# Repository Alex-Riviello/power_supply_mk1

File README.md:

# power_supply_mk1

## Description

Power supply created during ELE3000 - Personal project at Polytechnique Montreal (2017).  
The voltage is controlled by a PWM signal generated by a EFM8 Silicon Labs microcontroller. The signal is filtered and injected into the adjust pin of a LM337 and LM317 to generate a variable positive and negative voltage (got the idea from the EEVBlog#221 https://www.youtube.com/watch?v=CIGjActDeoM&t=860s). 

To communicate with the microcontroller, I used an Aardvark (USB to I2C Host Adapter). The voltage was set and the current was measured in real-time. Everything was displayed on a GUI made with PyQt.

## Project Details

TODO: Translate to english.

### Circuit Design

The PCB was designed using KiCAD. The KiCAD project can be found in the ./kicad_psu_mk1 directory.  
NOTE: This was one of my first PCB designs. I tried using many through-hole components to test them on a breadboard.

#### Schematic

#### PCB

#### Rectifier Bridge

A simple diode bridge was used to rectify the voltage coming out of the transformer.

#### Microcontroller

The EFM8BB1 microcontroller was used for this project. I chose this MCU since I had a couple laying around. A laptop communicates with the chip via I2C (and a USB to I2C adapter). I2C was used since it's a simple protocol that be used with a Raspberry Pi. The MCU also sends a PWM signal to the voltage regulators to modulate the output voltage.
2 ADCs are used to measure the voltage drop across a very small resistor to detect the current flowing through the outputs.

#### Positive voltage control

The voltage is controlled with a PWM signal which is filtered and amplified. An LM317 is used for the positive voltage and a LM337 is used for the negative voltage.

### GUI

The python GUI used is illustrated below. The voltage could be set and read in real-time. The code can be found in ./python_code. However, the hc file is not included (Aardvark interface), PyQt4 is no longer supported and the code runs in Python2. 

### Final Result

Overall, the PSU could provide upto 1.5 A of current at +/-2V to +/- 12.5V. The final circuit looked like this:

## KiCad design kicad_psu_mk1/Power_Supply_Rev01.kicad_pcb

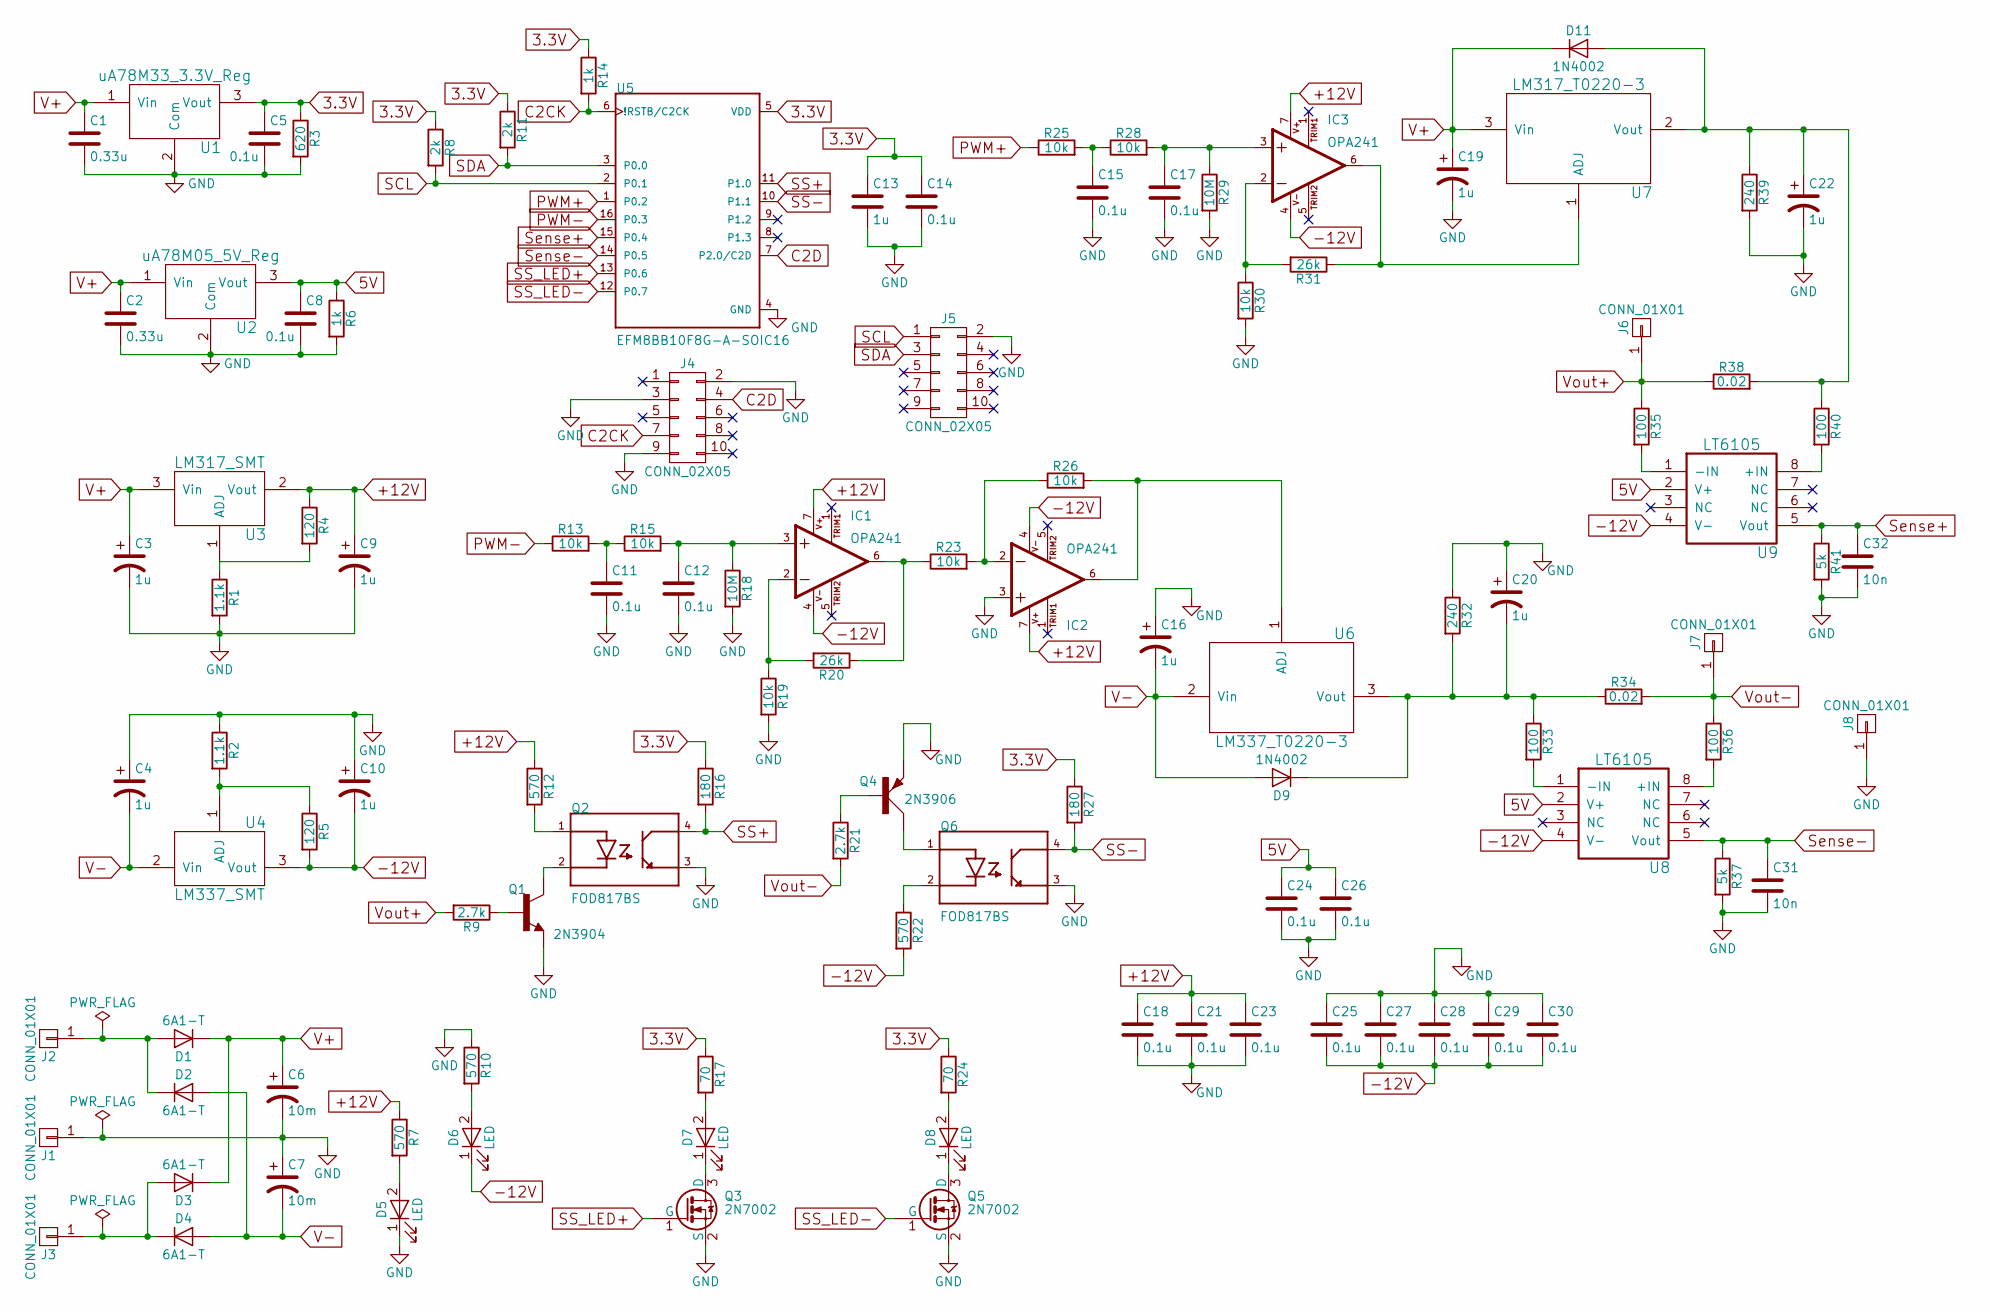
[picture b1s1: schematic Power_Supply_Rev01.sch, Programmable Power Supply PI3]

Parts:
C1, C2: 0.33u; C_0805_HandSoldering
C3, C4, C9, C10, C16, C19, C20, C22: 1u; CP_Tantalum_Case-A_EIA-3216-18_Hand
C5, C8, C11, C12, C14, C15, C17, C18, C21, C23, C24, C25, C26, C27, C28, C29, C30: 0.1u; C_0805_HandSoldering
C6, C7: 10m; CP_Radial_D22.0mm_P10.00mm_SnapIn
C13: 1u; C_0805_HandSoldering
C31, C32: 10n; C_0805_HandSoldering
D1, D2, D3, D4: 6A1-T; D_P600_R-6_P20.00mm_Horizontal
D5, D6, D7, D8: LED; LED_0805_HandSoldering
D9, D11: 1N4002; D_DO-41_SOD81_P7.62mm_Horizontal
IC1, IC2, IC3: OPA241; DIL08
J1, J2, J3, J6, J7, J8: CONN_01X01; SolderWirePad_single_SMD_5x10mm
J4, J5: CONN_02X05; Pin_Header_Straight_2x05_Pitch2.54mm
Q1: 2N3904; TO92
Q2, Q6: FOD817BS; SOIC254P1016X385-4N
Q3, Q5: 2N7002; SOT-23
Q4: 2N3906; TO92D
R1, R2: 1.1k; R_1206_HandSoldering
R3: 620; R_1206_HandSoldering
R4, R5: 120; R_1206_HandSoldering
R6, R14: 1k; R_1206_HandSoldering
R7, R10, R12, R22: 570; R_1206_HandSoldering
R8, R11: 2k; R_1206_HandSoldering
R9, R21: 2.7k; R_1206_HandSoldering
R13, R15, R19, R23, R25, R26, R28, R30: 10k; R_1206_HandSoldering
R16, R27: 180; R_1206_HandSoldering
R17, R24: 70; R_1206_HandSoldering
R18, R29: 10M; R_1206_HandSoldering
R20, R31: 26k; R_1206_HandSoldering
R32, R39: 240; R_2512_HandSoldering
R33, R35, R36, R40: 100; R_1206_HandSoldering
R34, R38: 0.02; R_1206_HandSoldering
R37, R41: 5k; R_1206_HandSoldering
U1: uA78M33_3.3V_Reg; SOT230P700X180-4N
U2: uA78M05_5V_Reg; SOT230P700X180-4N
U3: LM317_SMT; SOT230P700X180-4N
U4: LM337_SMT; SOT230P700X180-4N
U5: EFM8BB10F8G-A-SOIC16; SOIC127P600X175-16N
U6: LM337_T0220-3; TO-220-3_Horizontal
U7: LM317_T0220-3; TO-220-3_Horizontal
U8, U9: LT6105; MSOP-8_3x3mm_Pitch0.65mm

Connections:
3.3V: C5.1, C13.1, C14.1, R3.1, R8.1, R11.1, R14.1, R16.1, R17.1, R24.1, R27.1, U1.3 (Vout), U5.5 (VDD)
5V: C8.1, C24.1, C26.1, R6.1, U2.3 (Vout), U8.2 (V+), U9.2 (V+)
+12V: C9.1, C18.1, C21.1, C23.1, IC1.7 (V+), IC2.7 (V+), IC3.7 (V+), R4.1, R7.1, R12.1, U3.2 (Vout)
-12V: C10.2, C25.2, C27.2, C28.2, C29.2, C30.2, D6.1 (K), IC1.4 (V-), IC2.4 (V-), IC3.4 (V-), R5.2, R22.2, U4.3 (Vout), U8.4 (V-), U9.4 (V-)
C2CK: J4.7, R14.2, U5.6 (!RSTB/C2CK)
C2D: J4.4, U5.7 (P2.0/C2D)
GND: C1.2, C2.2, C3.2, C4.1, C5.2, C6.2, C7.1, C8.2, C9.2, C10.1, C11.2, C12.2, C13.2, C14.2, C15.2, C16.1, C17.2, C18.2, C19.2, C20.1, C21.2, C22.2, C23.2, C24.2, C25.1, C26.2, C27.1, C28.1, C29.1, C30.1, C31.2, C32.2, D5.1 (K), IC2.3 (+IN), J1.1, J4.2, J4.3, J4.9, J5.2, J8.1, Q1.3 (E), Q2.3 (EMITTER), Q3.2 (S), Q4.E, Q5.2 (S), Q6.3 (EMITTER), R1.2, R2.1, R3.2, R6.2, R10.1, R18.2, R19.2, R29.2, R30.2, R32.1, R37.2, R39.2, R41.2, U1.2 (Com), U2.2 (Com), U5.4 (GND)
unnamed: C11.1, R13.2, R15.1
unnamed: C12.1, IC1.3 (+IN), R15.2, R18.1
unnamed: C15.1, R25.2, R28.1
unnamed: C17.1, IC3.3 (+IN), R28.2, R29.1
unnamed: C20.2, D9.1 (K), R32.2, R33.1, R34.1, U6.3 (Vout)
unnamed: C22.1, D11.2 (A), R38.2, R39.1, R40.1, U7.2 (Vout)
unnamed: D1.2 (A), D2.1 (K), J2.1
unnamed: D3.2 (A), D4.1 (K), J3.1
unnamed: D5.2 (A), R7.2
unnamed: D6.2 (A), R10.2
unnamed: D7.1 (K), Q3.3 (D)
unnamed: D7.2 (A), R17.2
unnamed: D8.1 (K), Q5.3 (D)
unnamed: D8.2 (A), R24.2
unnamed: IC1.2 (-IN), R19.1, R20.2
unnamed: IC1.6 (OUT), R20.1, R23.1
unnamed: IC2.2 (-IN), R23.2, R26.1
unnamed: IC2.6 (OUT), R26.2, U6.1 (ADJ)
unnamed: IC3.2 (-IN), R30.1, R31.2
unnamed: IC3.6 (OUT), R31.1, U7.1 (ADJ)
unnamed: Q1.1 (C), Q2.2 (CATHODE)
unnamed: Q1.2 (B), R9.1
unnamed: Q2.1 (ANODE), R12.2
unnamed: Q4.B, R21.1
unnamed: Q4.C, Q6.1 (ANODE)
unnamed: Q6.2 (CATHODE), R22.1
unnamed: R1.1, R4.2, U3.1 (ADJ)
unnamed: R2.2, R5.1, U4.1 (ADJ)
unnamed: R33.2, U8.1 (-IN)
unnamed: R35.2, U9.1 (-IN)
unnamed: R36.2, U8.8 (+IN)
unnamed: R40.2, U9.8 (+IN)
PWM+: R25.1, U5.1 (P0.2)
PWM-: R13.1, U5.16 (P0.3)
SCL: J5.1, R8.2, U5.2 (P0.1)
SDA: J5.3, R11.2, U5.3 (P0.0)
SS+: Q2.4 (COLLECTOR), R16.2, U5.11 (P1.0)
SS-: Q6.4 (COLLECTOR), R27.2, U5.10 (P1.1)
SS_LED+: Q3.1 (G), U5.13 (P0.6)
SS_LED-: Q5.1 (G), U5.12 (P0.7)
Sense+: C32.1, R41.1, U5.15 (P0.4), U9.5 (Vout)
Sense-: C31.1, R37.1, U5.14 (P0.5), U8.5 (Vout)
V+: C1.1, C2.1, C3.1, C6.1, C19.1, D1.1 (K), D3.1 (K), D11.1 (K), U1.1 (Vin), U2.1 (Vin), U3.3 (Vin), U7.3 (Vin)
V-: C4.2, C7.2, C16.2, D2.2 (A), D4.2 (A), D9.2 (A), U4.2 (Vin), U6.2 (Vin)
Vout+: J6.1, R9.2, R35.1, R38.1
Vout-: J7.1, R21.2, R34.2, R36.1

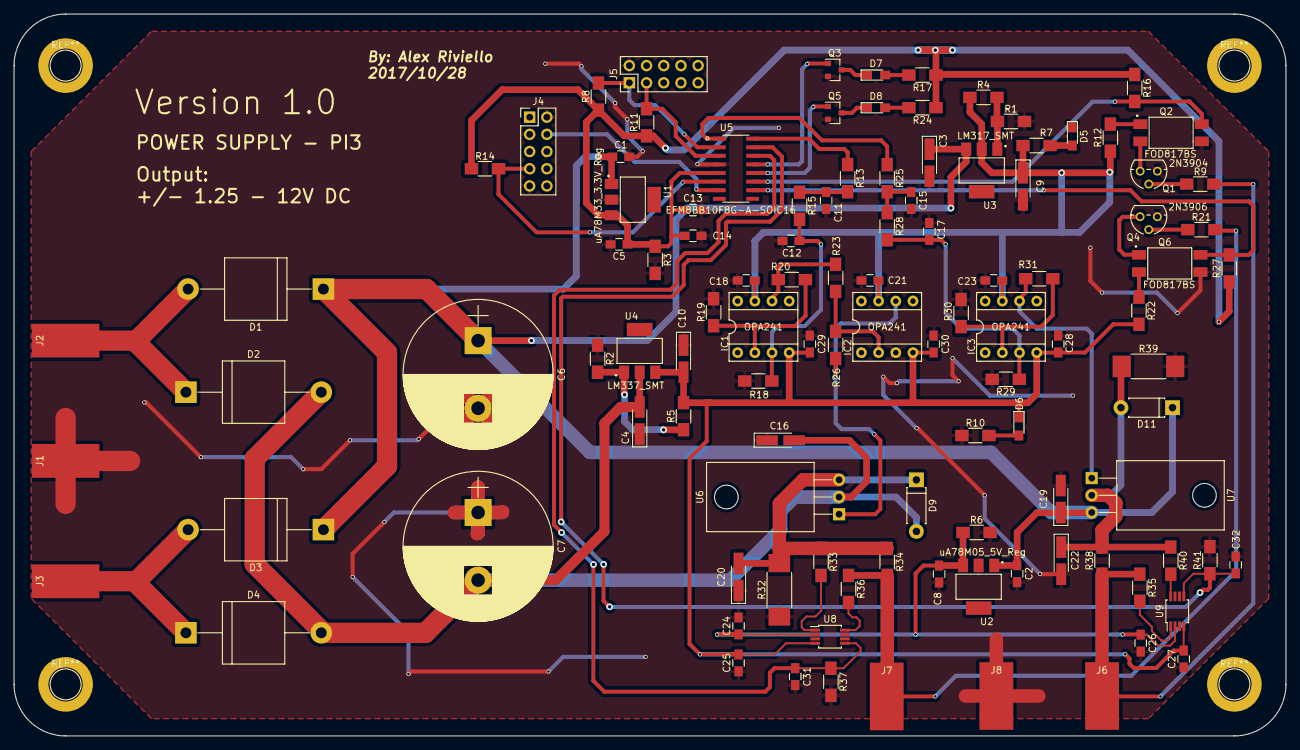
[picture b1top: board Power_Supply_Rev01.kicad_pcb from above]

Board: 2 copper layers, 188.0 x 106.7 mm, 109 parts (0 on the bottom side), 53 nets.

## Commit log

2020-07-14 Added project to repo
2020-07-14 Added picture of finished prototype
2020-07-14 Removed unnecessary file
